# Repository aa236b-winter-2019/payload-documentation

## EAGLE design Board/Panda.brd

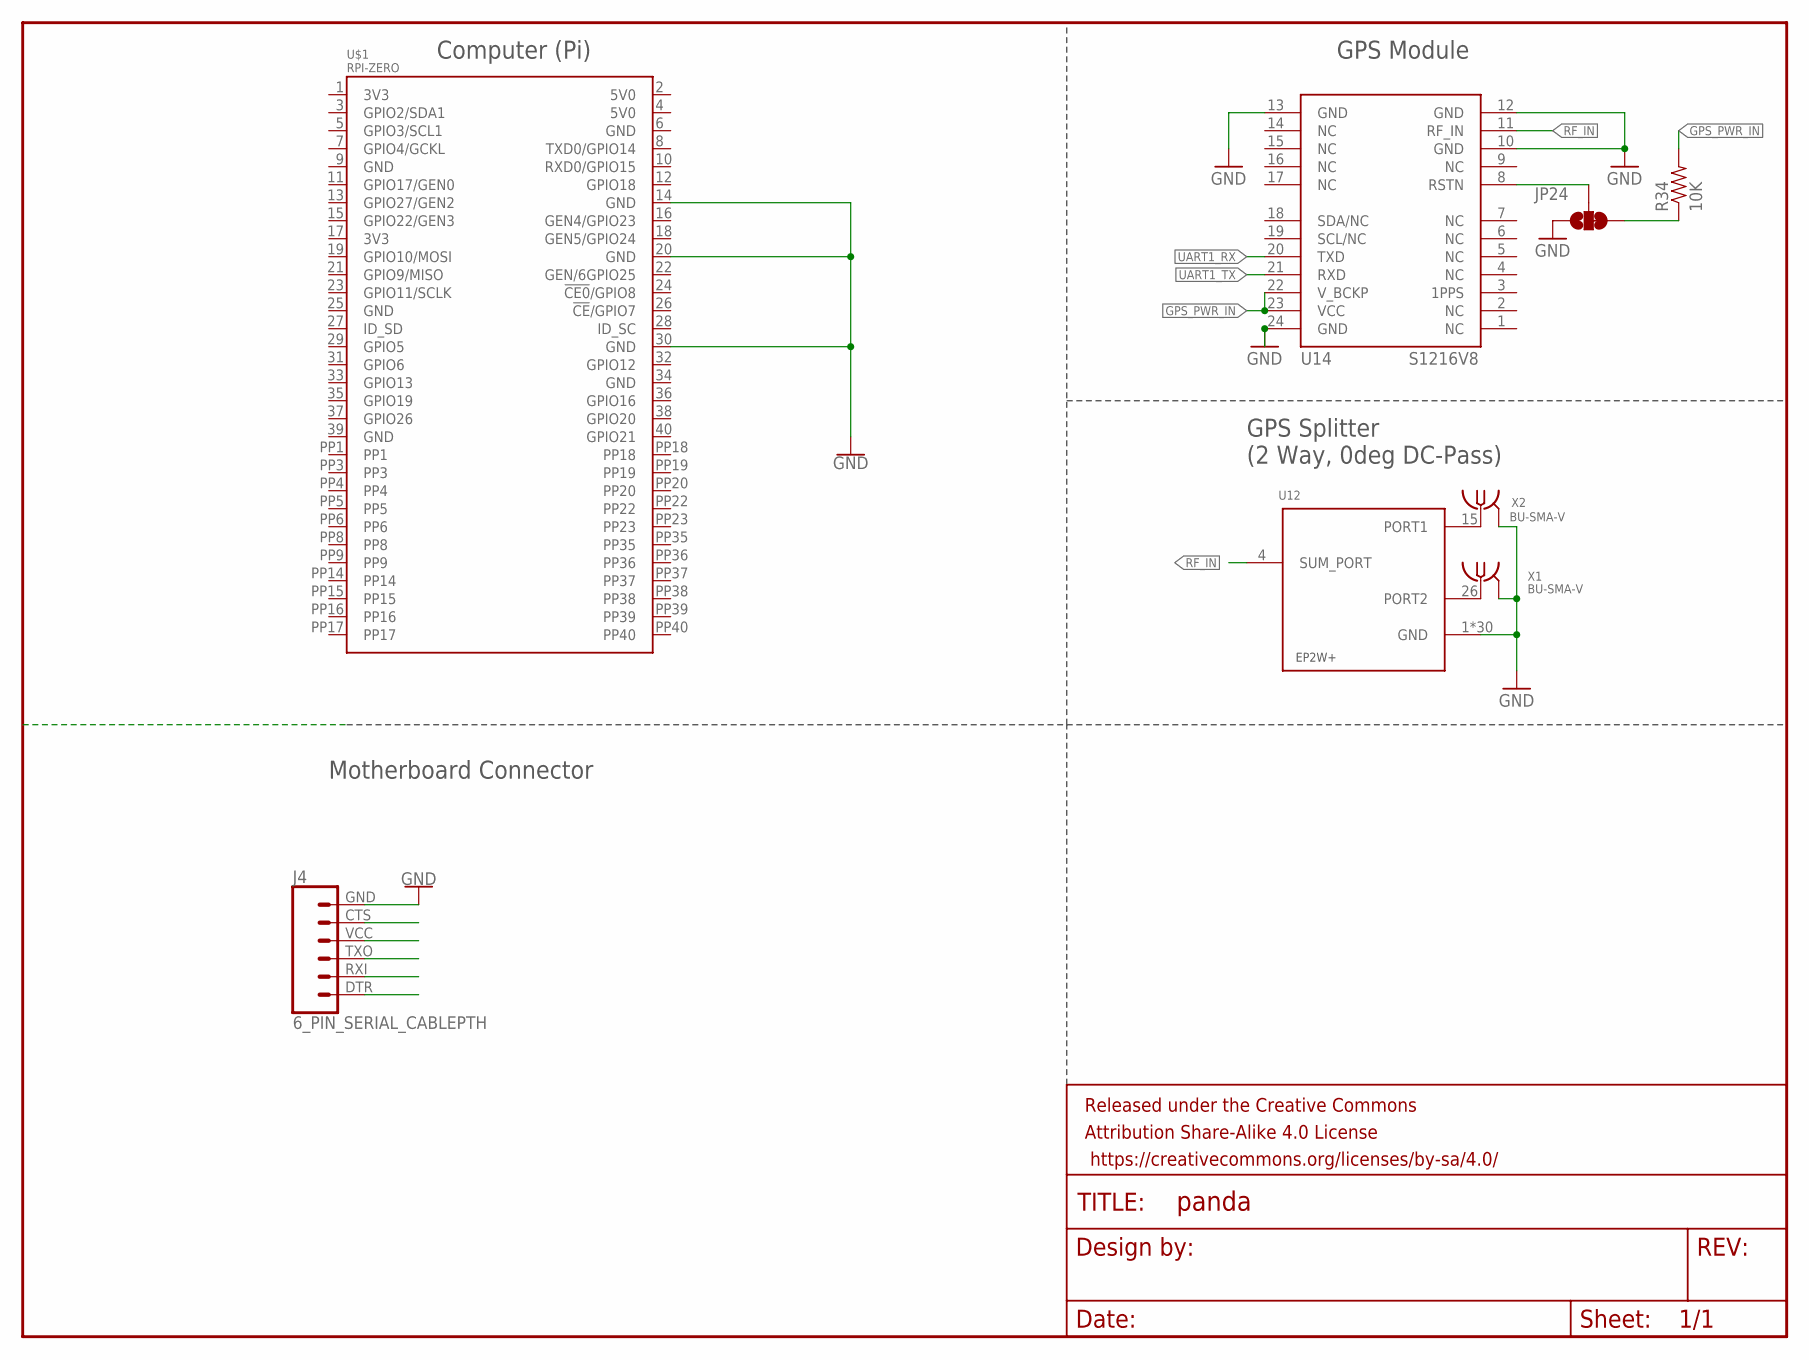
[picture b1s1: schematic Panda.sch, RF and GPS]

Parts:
FRAME2: FRAME-LETTER; CREATIVE_COMMONS
J4: 6_PIN_SERIAL_CABLEPTH; FTDI_BASIC
JP24: JUMPER-PAD-3-2OF3_NC_BY_TRACE_SMALL; PAD-JUMPER-3-2OF3_NC_BY_TRACE_YES_SILK_FULL_BOX
R34: 10K; 0603-RES
U12: EP2W+; QFN32-5X5MM
U14: S1216V8; S1216_24PIN_PACKAGE
U$1: RPI-ZERO; RASP_PI_ZERO_BOARD_FULL
X1, X2: BU-SMA-V

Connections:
GND: J4.GND (6), JP24.1, U12.1 (GND), U12.2 (GND), U12.3 (GND), U12.5 (GND), U12.6 (GND), U12.7 (GND), U12.8 (GND), U12.9 (GND), U12.10 (GND), U12.11 (GND), U12.12 (GND), U12.13 (GND), U12.14 (GND), U12.16 (GND), U12.17 (GND), U12.18 (GND), U12.19 (GND), U12.20 (GND), U12.21 (GND), U12.22 (GND), U12.23 (GND), U12.24 (GND), U12.25 (GND), U12.27 (GND), U12.28 (GND), U12.29 (GND), U12.30 (GND), U12.31 (GND), U12.32 (GND), U12.EP (GND), U14.10 (GND), U14.12 (GND), U14.13 (GND), U14.24 (GND), X1.2, X1.3 (2), X1.4 (2), X1.5 (2), X2.2, X2.3 (2), X2.4 (2), X2.5 (2)
GND@6: U$1.14 (GND), U$1.20 (GND), U$1.30 (GND)
GPS_PWR_IN: R34.2, U14.22 (V_BCKP), U14.23 (VCC)
unnamed: JP24.2, U14.8 (RSTN)
unnamed: U12.15 (PORT1), X2.1
unnamed: U12.26 (PORT2), X1.1
unnamed: JP24.3, R34.1
RF_IN: U12.4 (SUM_PORT), U14.11 (RF_IN)
UART1_RX: U14.20 (TXD)
UART1_TX: U14.21 (RXD)

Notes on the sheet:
GPS Module
GPS Splitter (2 Way, 0deg DC-Pass)
Computer (Pi)
Motherboard Connector

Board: 4 copper layers, 9 parts (4 on the bottom side), 8 nets, no tracks yet.

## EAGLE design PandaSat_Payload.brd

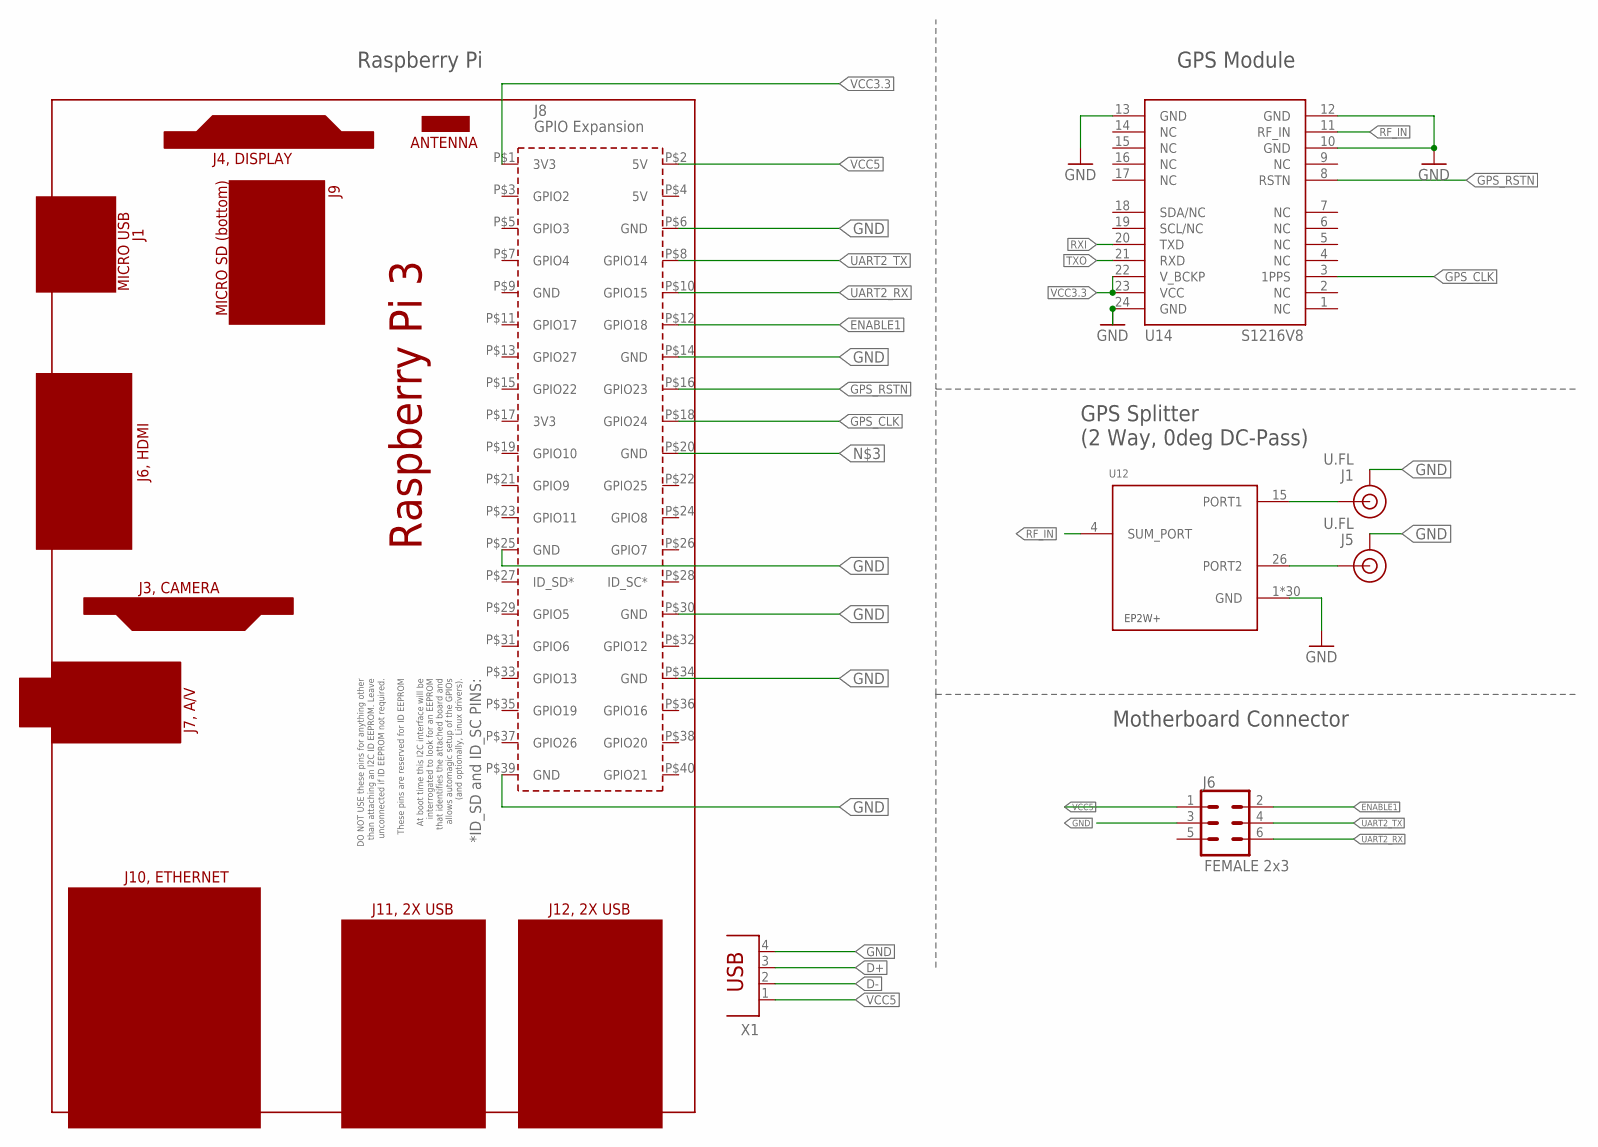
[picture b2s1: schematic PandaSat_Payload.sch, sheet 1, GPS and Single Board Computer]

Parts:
J1, J5: U.FL
J6: FEMALE 2x3; 2X3
PCB1: RPI3RPI3; RPI3
U12: EP2W+; QFN32-5X5MM
U14: S1216V8; S1216_24PIN_PACKAGE
X1: PN87520

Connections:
D+: X1.3; also elsewhere on the board
D-: X1.2; also elsewhere on the board
ENABLE1: J6.2, PCB1.P$12 (GPIO18)
GND: J1.1 (GND), J1.2 (GND), J5.1 (GND), J5.2 (GND), J6.3, PCB1.P$6 (GND), PCB1.P$14 (GND), PCB1.P$25 (GND), PCB1.P$30 (GND), PCB1.P$34 (GND), PCB1.P$39 (GND), U12.1 (GND), U12.2 (GND), U12.3 (GND), U12.5 (GND), U12.6 (GND), U12.7 (GND), U12.8 (GND), U12.9 (GND), U12.10 (GND), U12.11 (GND), U12.12 (GND), U12.13 (GND), U12.14 (GND), U12.16 (GND), U12.17 (GND), U12.18 (GND), U12.19 (GND), U12.20 (GND), U12.21 (GND), U12.22 (GND), U12.23 (GND), U12.24 (GND), U12.25 (GND), U12.27 (GND), U12.28 (GND), U12.29 (GND), U12.30 (GND), U12.31 (GND), U12.32 (GND), U12.EP (GND), U14.10 (GND), U14.12 (GND), U14.13 (GND), U14.24 (GND), X1.4; also elsewhere on the board
GPS_CLK: PCB1.P$18 (GPIO24), U14.3 (1PPS)
GPS_RSTN: PCB1.P$16 (GPIO23), U14.8 (RSTN)
RF_IN: U12.4 (SUM_PORT), U14.11 (RF_IN)
RXI: U14.20 (TXD); also elsewhere on the board
TXO: U14.21 (RXD); also elsewhere on the board
U.FL1: J1.FEED (SIGNAL), U12.15 (PORT1)
U.FL2: J5.FEED (SIGNAL), U12.26 (PORT2)
UART2_RX: J6.6, PCB1.P$10 (GPIO15)
UART2_TX: J6.4, PCB1.P$8 (GPIO14)
VCC3.3: PCB1.P$1 (3V3), U14.22 (V_BCKP), U14.23 (VCC)
VCC5: J6.1, PCB1.P$2 (5V), X1.1; also elsewhere on the board

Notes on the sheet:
GPS Module
GPS Splitter (2 Way, 0deg DC-Pass)
Motherboard Connector
Raspberry Pi

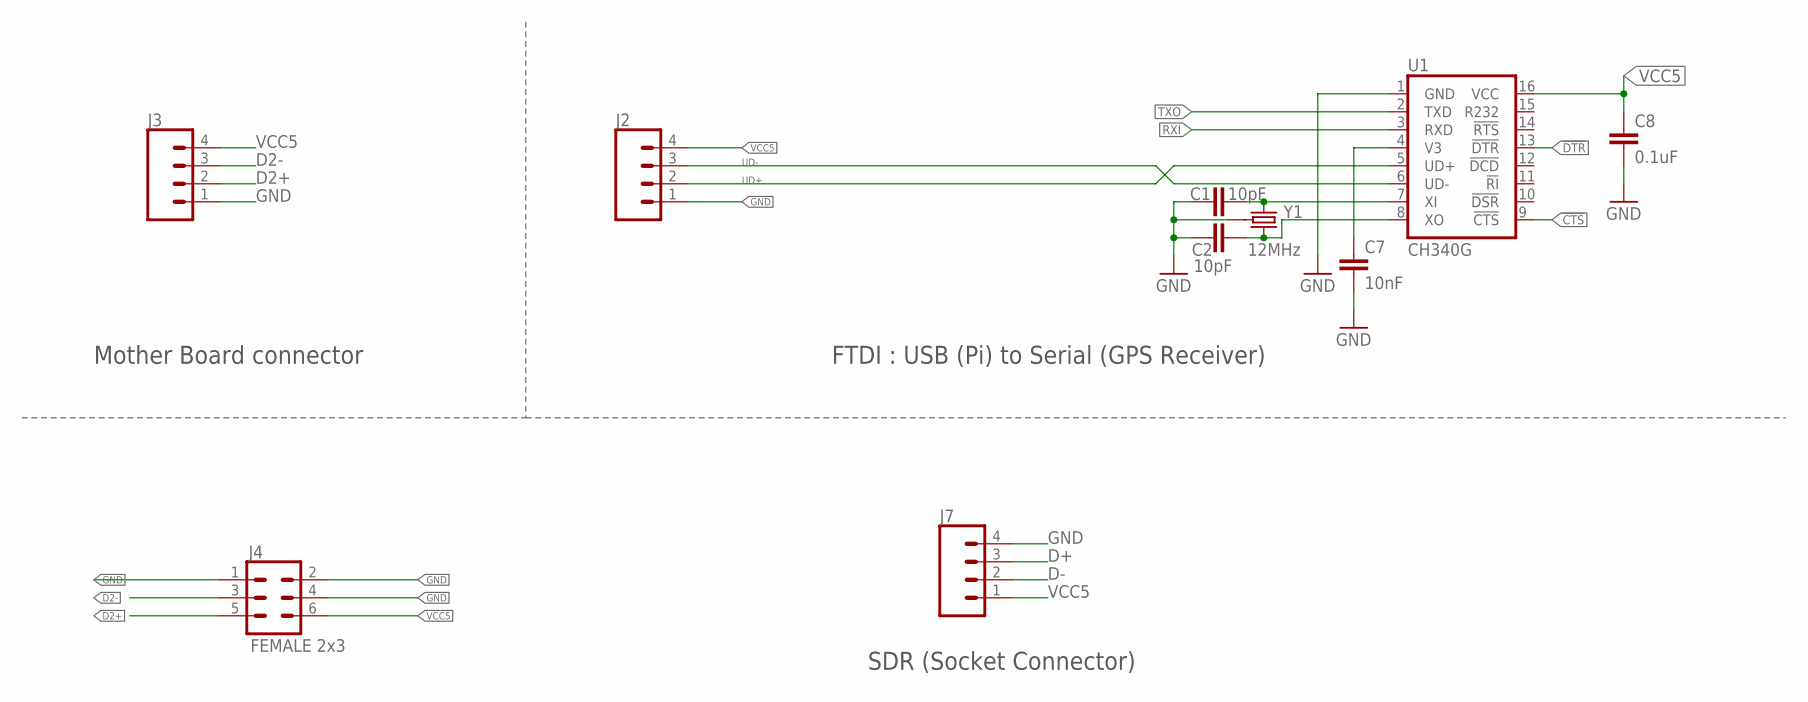
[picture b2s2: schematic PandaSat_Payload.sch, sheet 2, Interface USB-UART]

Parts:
C1, C2: 10pF; 0603-CAP
C7: 10nF; 0603-CAP
C8: 0.1uF; 0603-CAP
J2, J3, J7: CONN_04; 1X04
J4: FEMALE 2x3; 2X3
U1: CH340G; SO016
Y1: 12MHz; CRYSTAL-SMD-3.2X2.5

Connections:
!CTS: U1.9 (!CTS)
!DTR: U1.13 (!DTR)
D2+: J3.2, J4.5
D2-: J3.3, J4.3
D+: J7.3; also elsewhere on the board
D-: J7.2; also elsewhere on the board
GND: C1.1, C2.1, C7.2, C8.2, J2.1, J3.1, J4.1, J4.2, J4.4, J7.4, U1.1 (GND), Y1.2 (GND), Y1.4 (GND); also elsewhere on the board
unnamed: C2.2, U1.8 (XO), Y1.3 (2)
unnamed: C1.2, U1.7 (XI), Y1.1
RXI: U1.3 (RXD); also elsewhere on the board
TXO: U1.2 (TXD); also elsewhere on the board
UD+: J2.2, U1.5 (UD+)
UD-: J2.3, U1.6 (UD-)
V1: C7.1, U1.4 (V3)
VCC5: C8.1, J2.4, J3.4, J4.6, J7.1, U1.16 (VCC); also elsewhere on the board

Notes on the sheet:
FTDI : USB (Pi) to Serial (GPS Receiver)
Mother Board connector
SDR (Socket Connector)

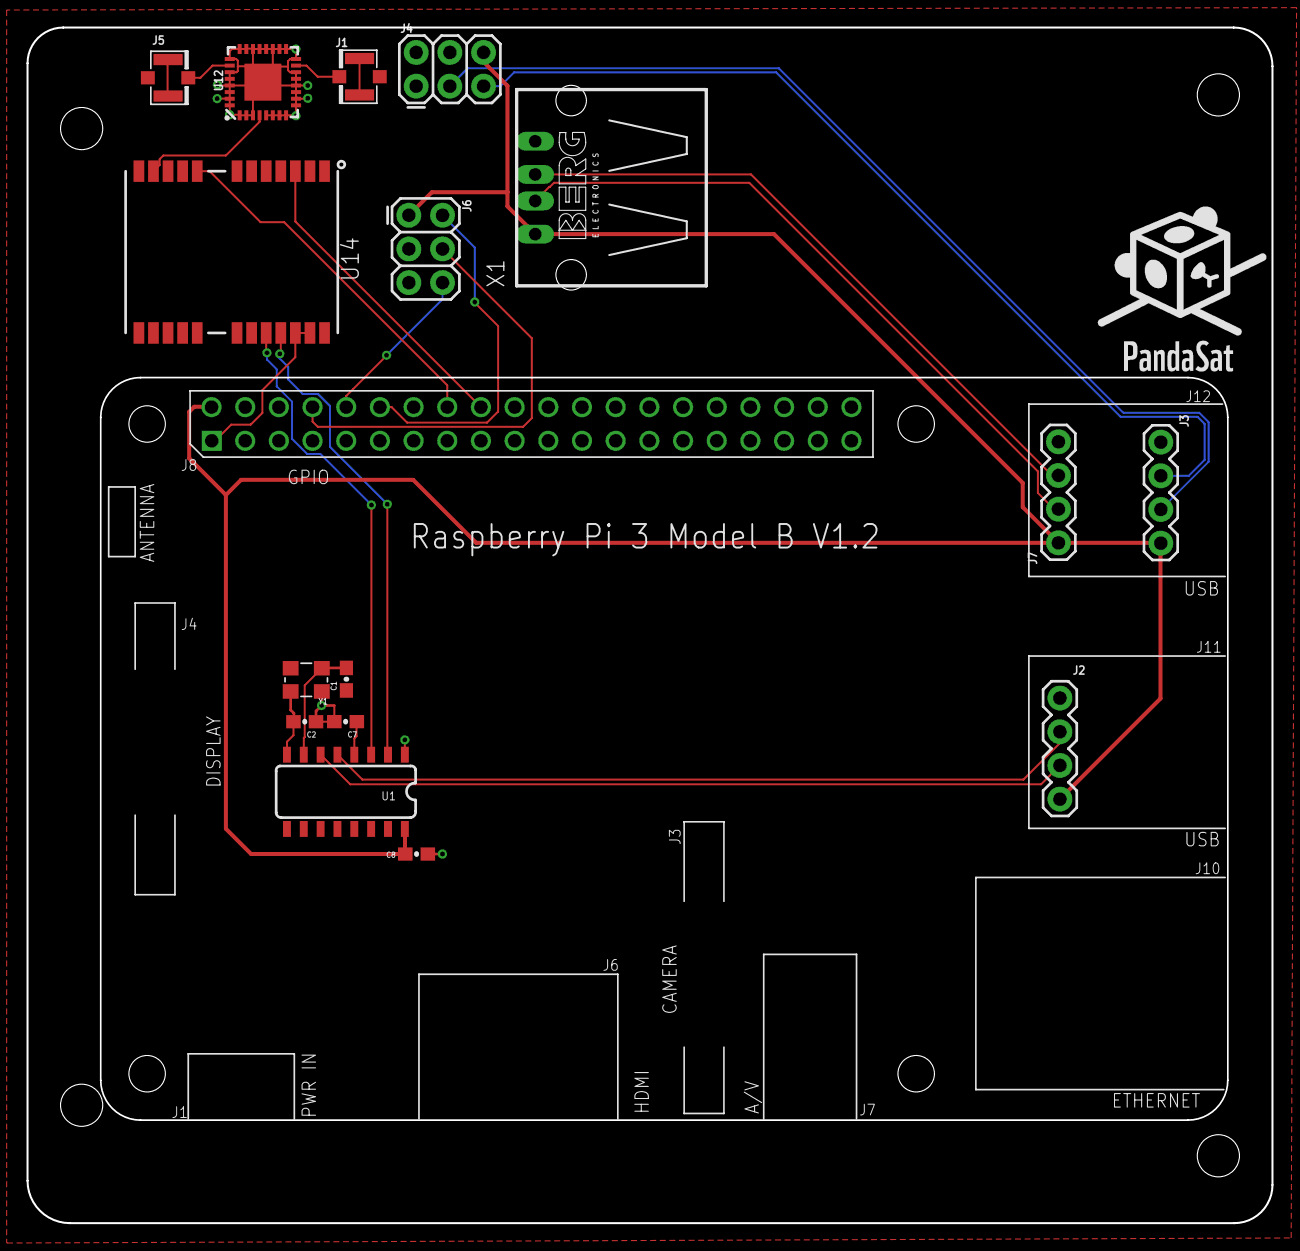
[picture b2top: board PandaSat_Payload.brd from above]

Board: 2 copper layers, 93.9 x 90.2 mm, 17 parts (0 on the bottom side), 22 nets.

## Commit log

2019-01-12 Create Requirements
2019-01-12 Rename Requirements to Requirements.md
2019-01-13 Create GPS Data Sheet
2019-01-13 Create References
2019-01-13 Create test
2019-01-14 Added Nooelec NESDR SMArt XTR SDR Datasheet
2019-01-25 Adding julia files from tag simulations
2019-01-25 Adding tag simulation Julia code
2019-01-25 Put into folder
2019-01-29 Added Block Diagram Image
2019-01-31 Add files via upload
    Added draft PCB
2019-02-07 Added PandaSat_Payload schematic and board
    -Finishing routing needed
2019-02-08 Added oshspark Design Check Rule file
2019-02-08 Adding last version of Panda_Payload PCB
2019-02-11 added image vertical profile payload board
2019-02-11 update diagram
2019-02-20 FFT testing with GNU Radio
2019-02-21 Saving FFT value to binary file
2019-02-24 first test transmit receive with two SDR
2019-02-24 update vertical profile, fixed error
2019-02-24 Added Assembly file Payload Board Solidworks
2019-02-24 Added part file from CAD eagle
2019-02-25 added new version of transmit grc with bug fixes
2019-02-26 Added Last version of PandaSat_Payload sch/board
2019-02-26 update receive
2019-02-26 transmittor working
2019-02-26 working receive
2019-02-27 added emn, emp files from EAGLE
2019-02-27 Added parts of the assembly PANDASAT CAD
2019-02-27 New version parts CAD Payload
2019-02-27 Added V3 of Payload CAD
2019-03-03 Added changes to the EAGLE files on the board
    changed position of the SDR USB socket
    changed the position of the USB 4 pins connector (closer to the Pi holes)
2019-03-04 Added last changes for new board
    vias diameters
2019-03-04 Added CAM DATA Board
2019-03-04 Added Logo to Eagle CAD
2019-03-04 CAM data added logo
2019-03-10 Cleaning up repo
2019-03-10 Linear freq tracker working
2019-03-10 Cleaning up, archived old files, clear names
2019-03-12 added rational resampler for receive
2019-03-12 Ratioanl resampler transmit
2019-03-12 Added new Eagle Files for payload board
    -modified pins USB socket
    -added 4 pins connector (socket - Pi)
2019-03-16 added pictures/schematic for description section
2019-03-16 sdr picture
2019-03-16 ftdi image
2019-03-16 PC104 dim
2019-03-16 connector eagle
2019-03-16 pi pic
2019-03-16 board rev 1
2019-03-16 vertical profile
2019-03-16 cad picture
2019-03-16 panda logo
2019-03-16 logo pandasat jpeg
2019-03-18 Create DopplerSpoof.m
    creating matlab folder for spoofing codes
2019-03-18 Dopple spoofing codes
2019-03-18 Adding postion estimation code
2019-03-18 CPFSK info
2019-03-21 Create placeholder
2019-03-21 organized repo
2019-03-21 organized repo pt 2

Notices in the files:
parts and their libraries:
SparkFun-Passives: Licensing: Creative Commons ShareAlike 4.0 International - https://creativecommons.org/licenses/by-sa/4.0
SparkFun-Aesthetics: Released under the Creative Commons Attribution Share-Alike 4.0 License
SparkFun-Aesthetics: https://creativecommons.org/licenses/by-sa/4.0
